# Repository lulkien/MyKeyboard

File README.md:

# My Custom Mechanical Keyboard

This is the design for my custom TLK, where I'm gonna make my own keyboard from scratch with hotswap controller.

(I have no idea why I'm doing this but it's kinda cool)

## Todo:

- [x] PCB Design (Kicad 8)
- [x] Case Design (OpenSCAD)
- [x] Firmware (use Rust)

## References:

- [Joe Scotto's guide for the PCB design](https://www.youtube.com/watch?v=7LyziNdFlew&list=PLBD2IS_t_iWZDMdG_ZF57x9Ebm3kxKqxF) (recommend to watch this playlist first)

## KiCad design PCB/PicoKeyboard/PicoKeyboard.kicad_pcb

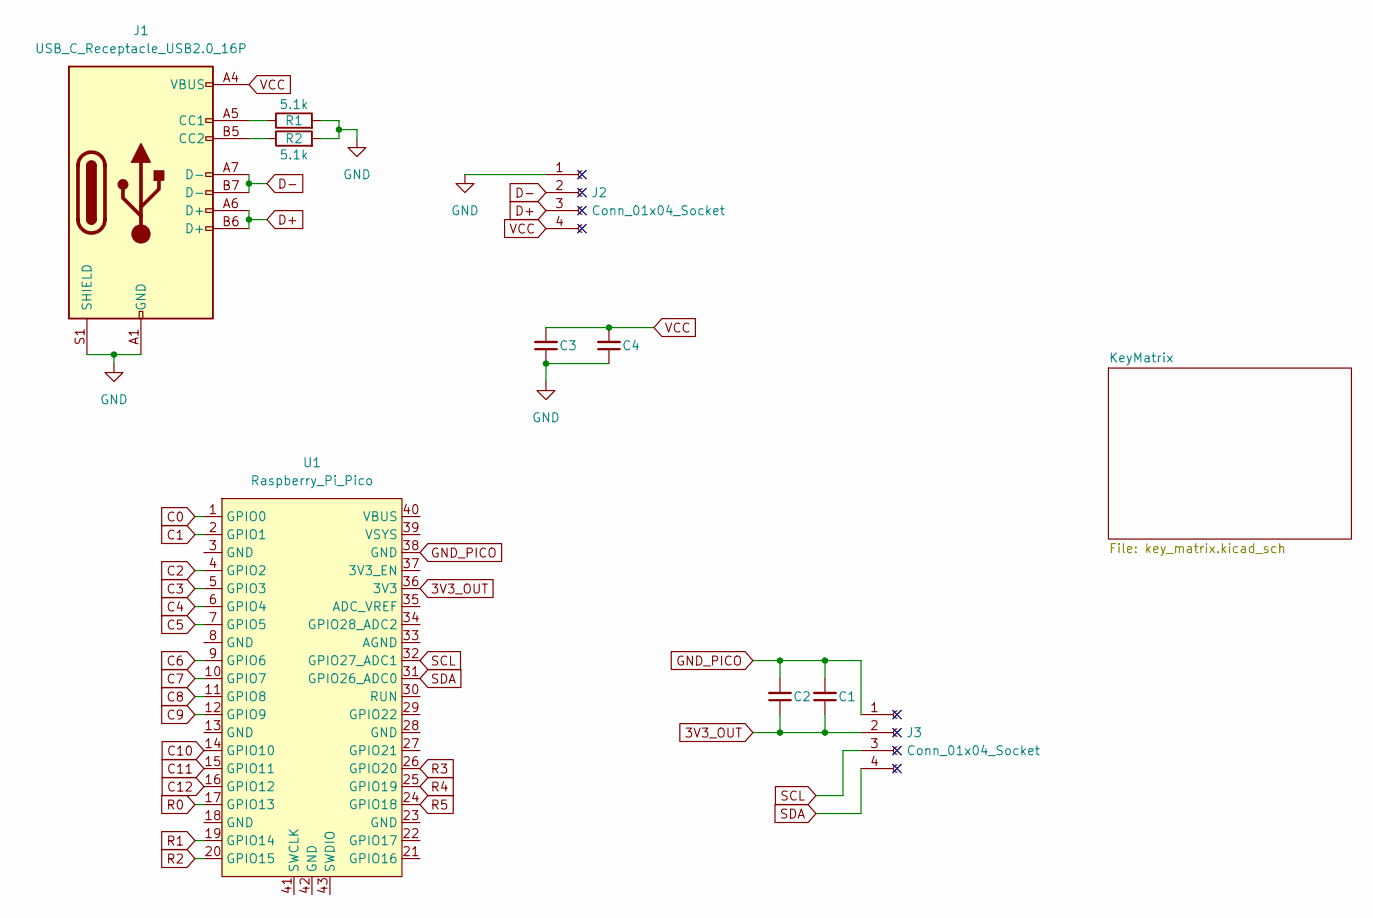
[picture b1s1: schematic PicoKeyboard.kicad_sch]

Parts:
C1, C4: 100nF; C_0603_1608Metric
C2, C3: 1uF; C_0603_1608Metric
J1: USB_C_Receptacle_USB2.0_16P; USB_C_Receptacle_HCTL_HC-TYPE-C-16P-01A
J2: Conn_01x04_Socket; PinHeader_1x04_P2.54mm_Vertical
J3: Conn_01x04_Socket; PinSocket_1x04_P2.54mm_Vertical
R1, R2: 5.1k; R_0603_1608Metric
U1: Raspberry_Pi_Pico

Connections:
3V3_OUT: C1.1, C2.1, J3.2, U1.36 (3V3)
C0: U1.1 (GPIO0); also elsewhere on the board
C1: U1.2 (GPIO1); also elsewhere on the board
C2: U1.4 (GPIO2); also elsewhere on the board
C3: U1.5 (GPIO3); also elsewhere on the board
C4: U1.6 (GPIO4); also elsewhere on the board
C5: U1.7 (GPIO5); also elsewhere on the board
C6: U1.9 (GPIO6); also elsewhere on the board
C7: U1.10 (GPIO7); also elsewhere on the board
C8: U1.11 (GPIO8); also elsewhere on the board
C9: U1.12 (GPIO9); also elsewhere on the board
C10: U1.14 (GPIO10); also elsewhere on the board
C11: U1.15 (GPIO11); also elsewhere on the board
C12: U1.16 (GPIO12); also elsewhere on the board
D+: J1.A6 (D+), J1.B6 (D+), J2.3
D-: J1.A7 (D-), J1.B7 (D-), J2.2
GND: C3.1, C4.1, J1.A1 (GND), J1.A12 (GND), J1.B1 (GND), J1.B12 (GND), J1.S1 (SHIELD), J2.1, R1.2, R2.2
GND_PICO: C1.2, C2.2, J3.1, U1.38 (GND)
unnamed: J1.A5 (CC1), R1.1
unnamed: J1.B5 (CC2), R2.1
R0: U1.17 (GPIO13); also elsewhere on the board
R1: U1.19 (GPIO14); also elsewhere on the board
R2: U1.20 (GPIO15); also elsewhere on the board
R3: U1.26 (GPIO20); also elsewhere on the board
R4: U1.25 (GPIO19); also elsewhere on the board
R5: U1.24 (GPIO18); also elsewhere on the board
SCL: J3.3, U1.32 (GPIO27_ADC1)
SDA: J3.4, U1.31 (GPIO26_ADC0)
VCC: C3.2, C4.2, J1.A4 (VBUS), J1.A9 (VBUS), J1.B4 (VBUS), J1.B9 (VBUS), J2.4

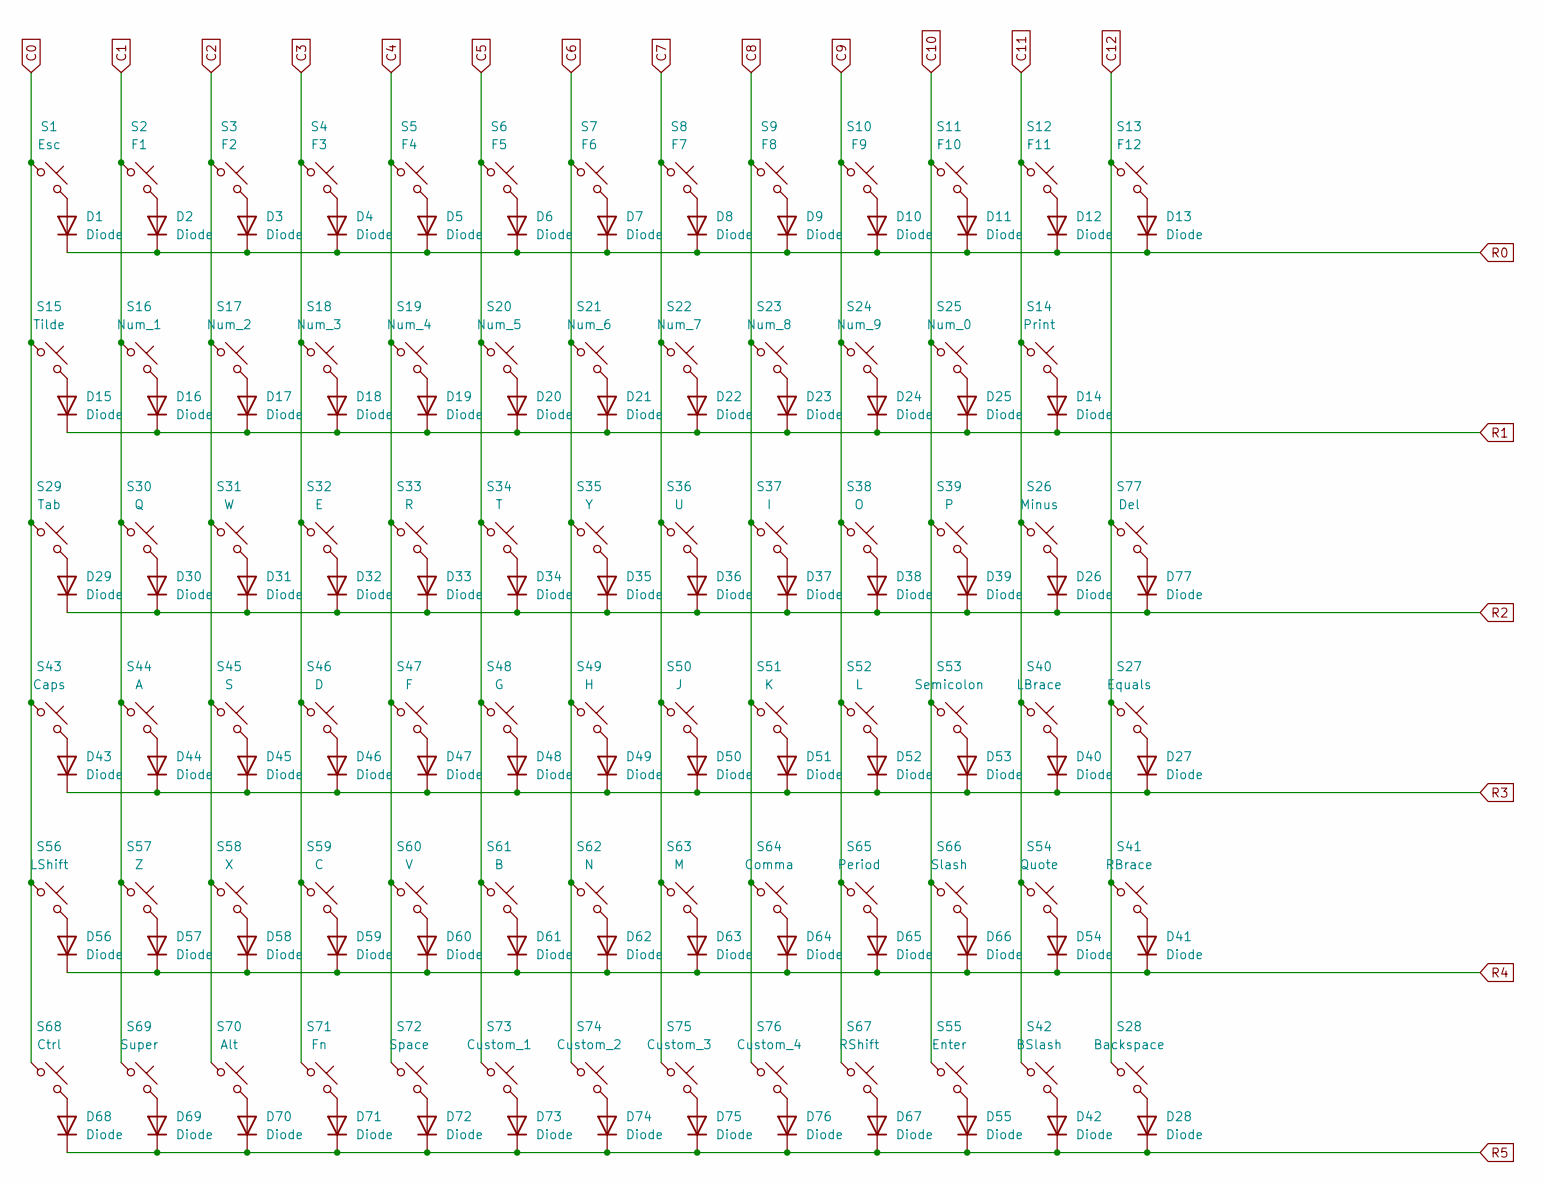
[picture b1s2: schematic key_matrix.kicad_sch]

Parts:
D1, D2, D3, D4, D5, D6, D7, D8, D9, D10, D11, D12, D13, D14, D15, D16, D17, D18, D19, D20, D21, D22, D23, D24, D25, D26, D27, D28, D29, D30, D31, D32, D33, D34, D35, D36, D37, D38, D39, D40, D41, D42, D43, D44, D45, D46, D47, D48, D49, D50, D51, D52, D53, D54, D55, D56, D57, D58, D59, D60, D61, D62, D63, D64, D65, D66, D67, D68, D69, D70, D71, D72, D73, D74, D75, D76, D77: Diode; Diode_SOD-123
S1: Esc; Hotswap_MX_1.00u
S2: F1; Hotswap_MX_1.00u
S3: F2; Hotswap_MX_1.00u
S4: F3; Hotswap_MX_1.00u
S5: F4; Hotswap_MX_1.00u
S6: F5; Hotswap_MX_1.00u
S7: F6; Hotswap_MX_1.00u
S8: F7; Hotswap_MX_1.00u
S9: F8; Hotswap_MX_1.00u
S10: F9; Hotswap_MX_1.00u
S11: F10; Hotswap_MX_1.00u
S12: F11; Hotswap_MX_1.00u
S13: F12; Hotswap_MX_1.00u
S14: Print; Hotswap_MX_1.00u
S15: Tilde; Hotswap_MX_1.00u
S16: Num_1; Hotswap_MX_1.00u
S17: Num_2; Hotswap_MX_1.00u
S18: Num_3; Hotswap_MX_1.00u
S19: Num_4; Hotswap_MX_1.00u
S20: Num_5; Hotswap_MX_1.00u
S21: Num_6; Hotswap_MX_1.00u
S22: Num_7; Hotswap_MX_1.00u
S23: Num_8; Hotswap_MX_1.00u
S24: Num_9; Hotswap_MX_1.00u
S25: Num_0; Hotswap_MX_1.00u
S26: Minus; Hotswap_MX_1.00u
S27: Equals; Hotswap_MX_1.00u
S28: Backspace; Hotswap_MX_2.00u
S29: Tab; Hotswap_MX_1.50u
S30: Q; Hotswap_MX_1.00u
S31: W; Hotswap_MX_1.00u
S32: E; Hotswap_MX_1.00u
S33: R; Hotswap_MX_1.00u
S34: T; Hotswap_MX_1.00u
S35: Y; Hotswap_MX_1.00u
S36: U; Hotswap_MX_1.00u
S37: I; Hotswap_MX_1.00u
S38: O; Hotswap_MX_1.00u
S39: P; Hotswap_MX_1.00u
S40: LBrace; Hotswap_MX_1.00u
S41: RBrace; Hotswap_MX_1.00u
S42: BSlash; Hotswap_MX_1.50u
S43: Caps; Hotswap_MX_1.75u
S44: A; Hotswap_MX_1.00u
S45: S; Hotswap_MX_1.00u
S46: D; Hotswap_MX_1.00u
S47: F; Hotswap_MX_1.00u
S48: G; Hotswap_MX_1.00u
S49: H; Hotswap_MX_1.00u
S50: J; Hotswap_MX_1.00u
S51: K; Hotswap_MX_1.00u
S52: L; Hotswap_MX_1.00u
S53: Semicolon; Hotswap_MX_1.00u
S54: Quote; Hotswap_MX_1.00u
S55: Enter; Hotswap_MX_2.25u
S56: LShift; Hotswap_MX_2.25u
S57: Z; Hotswap_MX_1.00u
S58: X; Hotswap_MX_1.00u
S59: C; Hotswap_MX_1.00u
S60: V; Hotswap_MX_1.00u
S61: B; Hotswap_MX_1.00u
S62: N; Hotswap_MX_1.00u
S63: M; Hotswap_MX_1.00u
S64: Comma; Hotswap_MX_1.00u
S65: Period; Hotswap_MX_1.00u
S66: Slash; Hotswap_MX_1.00u
S67: RShift; Hotswap_MX_2.75u
S68: Ctrl; Hotswap_MX_1.25u
S69: Super; Hotswap_MX_1.25u
S70: Alt; Hotswap_MX_1.25u
S71: Fn; Hotswap_MX_1.00u
S72: Space; Hotswap_MX_6.25u
S73: Custom_1; Hotswap_MX_1.00u
S74: Custom_2; Hotswap_MX_1.00u
S75: Custom_3; Hotswap_MX_1.00u
S76: Custom_4; Hotswap_MX_1.00u
S77: Del; Hotswap_MX_1.00u

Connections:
C0: S1.1, S15.1, S29.1, S43.1, S56.1, S68.1; also elsewhere on the board
C1: S2.1, S16.1, S30.1, S44.1, S57.1, S69.1; also elsewhere on the board
C2: S3.1, S17.1, S31.1, S45.1, S58.1, S70.1; also elsewhere on the board
C3: S4.1, S18.1, S32.1, S46.1, S59.1, S71.1; also elsewhere on the board
C4: S5.1, S19.1, S33.1, S47.1, S60.1, S72.1; also elsewhere on the board
C5: S6.1, S20.1, S34.1, S48.1, S61.1, S73.1; also elsewhere on the board
C6: S7.1, S21.1, S35.1, S49.1, S62.1, S74.1; also elsewhere on the board
C7: S8.1, S22.1, S36.1, S50.1, S63.1, S75.1; also elsewhere on the board
C8: S9.1, S23.1, S37.1, S51.1, S64.1, S76.1; also elsewhere on the board
C9: S10.1, S24.1, S38.1, S52.1, S65.1, S67.1; also elsewhere on the board
C10: S11.1, S25.1, S39.1, S53.1, S55.1, S66.1; also elsewhere on the board
C11: S12.1, S14.1, S26.1, S40.1, S42.1, S54.1; also elsewhere on the board
C12: S13.1, S27.1, S28.1, S41.1, S77.1; also elsewhere on the board
unnamed: D1.2 (A), S1.2
unnamed: D2.2 (A), S2.2
unnamed: D3.2 (A), S3.2
unnamed: D4.2 (A), S4.2
unnamed: D5.2 (A), S5.2
unnamed: D6.2 (A), S6.2
unnamed: D7.2 (A), S7.2
unnamed: D8.2 (A), S8.2
unnamed: D9.2 (A), S9.2
unnamed: D10.2 (A), S10.2
unnamed: D11.2 (A), S11.2
unnamed: D12.2 (A), S12.2
unnamed: D13.2 (A), S13.2
unnamed: D14.2 (A), S14.2
unnamed: D15.2 (A), S15.2
unnamed: D16.2 (A), S16.2
unnamed: D17.2 (A), S17.2
unnamed: D18.2 (A), S18.2
unnamed: D19.2 (A), S19.2
unnamed: D20.2 (A), S20.2
unnamed: D21.2 (A), S21.2
unnamed: D22.2 (A), S22.2
unnamed: D23.2 (A), S23.2
unnamed: D24.2 (A), S24.2
unnamed: D25.2 (A), S25.2
unnamed: D26.2 (A), S26.2
unnamed: D27.2 (A), S27.2
unnamed: D28.2 (A), S28.2
unnamed: D29.2 (A), S29.2
unnamed: D30.2 (A), S30.2
unnamed: D31.2 (A), S31.2
unnamed: D32.2 (A), S32.2
unnamed: D33.2 (A), S33.2
unnamed: D34.2 (A), S34.2
unnamed: D35.2 (A), S35.2
unnamed: D36.2 (A), S36.2
unnamed: D37.2 (A), S37.2
unnamed: D38.2 (A), S38.2
unnamed: D39.2 (A), S39.2
unnamed: D40.2 (A), S40.2
unnamed: D41.2 (A), S41.2
unnamed: D42.2 (A), S42.2
unnamed: D43.2 (A), S43.2
unnamed: D44.2 (A), S44.2
unnamed: D45.2 (A), S45.2
unnamed: D46.2 (A), S46.2
unnamed: D47.2 (A), S47.2
unnamed: D48.2 (A), S48.2
unnamed: D49.2 (A), S49.2
unnamed: D50.2 (A), S50.2
unnamed: D51.2 (A), S51.2
unnamed: D52.2 (A), S52.2
unnamed: D53.2 (A), S53.2
unnamed: D54.2 (A), S54.2
unnamed: D55.2 (A), S55.2
unnamed: D56.2 (A), S56.2
unnamed: D57.2 (A), S57.2
unnamed: D58.2 (A), S58.2
unnamed: D59.2 (A), S59.2
unnamed: D60.2 (A), S60.2
unnamed: D61.2 (A), S61.2
unnamed: D62.2 (A), S62.2
unnamed: D63.2 (A), S63.2
unnamed: D64.2 (A), S64.2
unnamed: D65.2 (A), S65.2
unnamed: D66.2 (A), S66.2
unnamed: D67.2 (A), S67.2
unnamed: D68.2 (A), S68.2
unnamed: D69.2 (A), S69.2
unnamed: D70.2 (A), S70.2
unnamed: D71.2 (A), S71.2
unnamed: D72.2 (A), S72.2
unnamed: D73.2 (A), S73.2
unnamed: D74.2 (A), S74.2
unnamed: D75.2 (A), S75.2
unnamed: D76.2 (A), S76.2
unnamed: D77.2 (A), S77.2
R0: D1.1 (K), D2.1 (K), D3.1 (K), D4.1 (K), D5.1 (K), D6.1 (K), D7.1 (K), D8.1 (K), D9.1 (K), D10.1 (K), D11.1 (K), D12.1 (K), D13.1 (K); also elsewhere on the board
R1: D14.1 (K), D15.1 (K), D16.1 (K), D17.1 (K), D18.1 (K), D19.1 (K), D20.1 (K), D21.1 (K), D22.1 (K), D23.1 (K), D24.1 (K), D25.1 (K); also elsewhere on the board
R2: D26.1 (K), D29.1 (K), D30.1 (K), D31.1 (K), D32.1 (K), D33.1 (K), D34.1 (K), D35.1 (K), D36.1 (K), D37.1 (K), D38.1 (K), D39.1 (K), D77.1 (K); also elsewhere on the board
R3: D27.1 (K), D40.1 (K), D43.1 (K), D44.1 (K), D45.1 (K), D46.1 (K), D47.1 (K), D48.1 (K), D49.1 (K), D50.1 (K), D51.1 (K), D52.1 (K), D53.1 (K); also elsewhere on the board
R4: D41.1 (K), D54.1 (K), D56.1 (K), D57.1 (K), D58.1 (K), D59.1 (K), D60.1 (K), D61.1 (K), D62.1 (K), D63.1 (K), D64.1 (K), D65.1 (K), D66.1 (K); also elsewhere on the board
R5: D28.1 (K), D42.1 (K), D55.1 (K), D67.1 (K), D68.1 (K), D69.1 (K), D70.1 (K), D71.1 (K), D72.1 (K), D73.1 (K), D74.1 (K), D75.1 (K), D76.1 (K); also elsewhere on the board

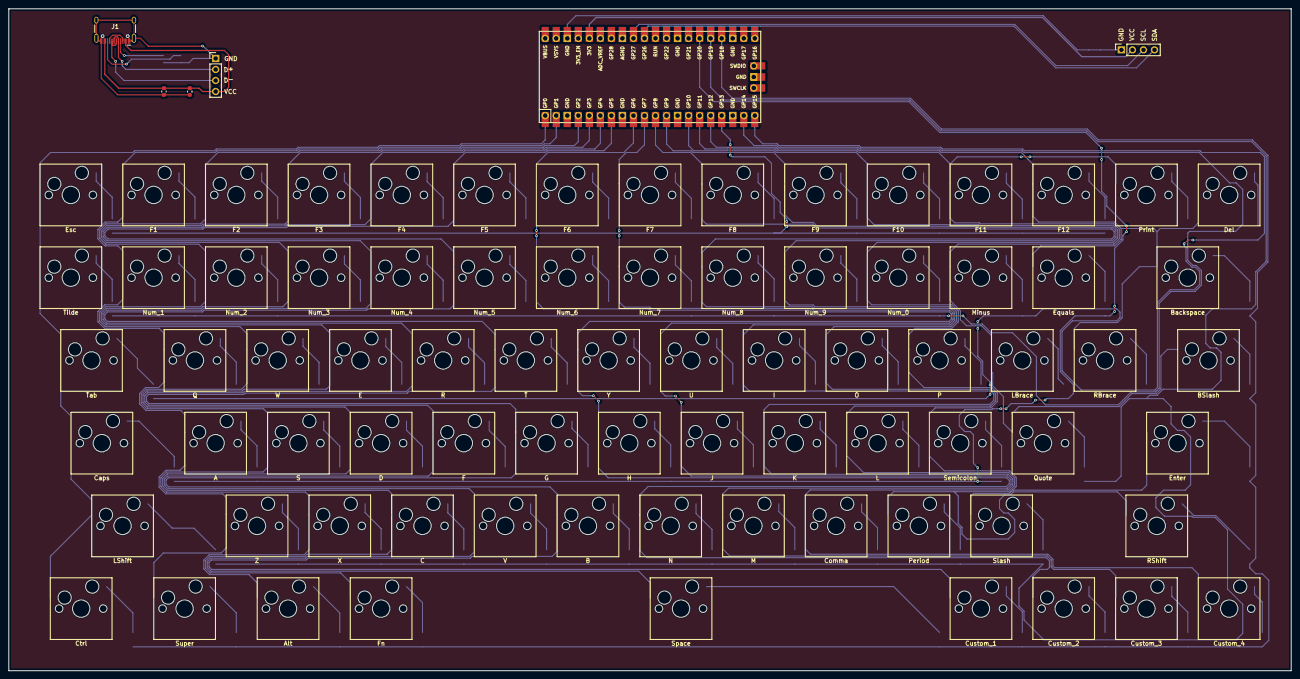
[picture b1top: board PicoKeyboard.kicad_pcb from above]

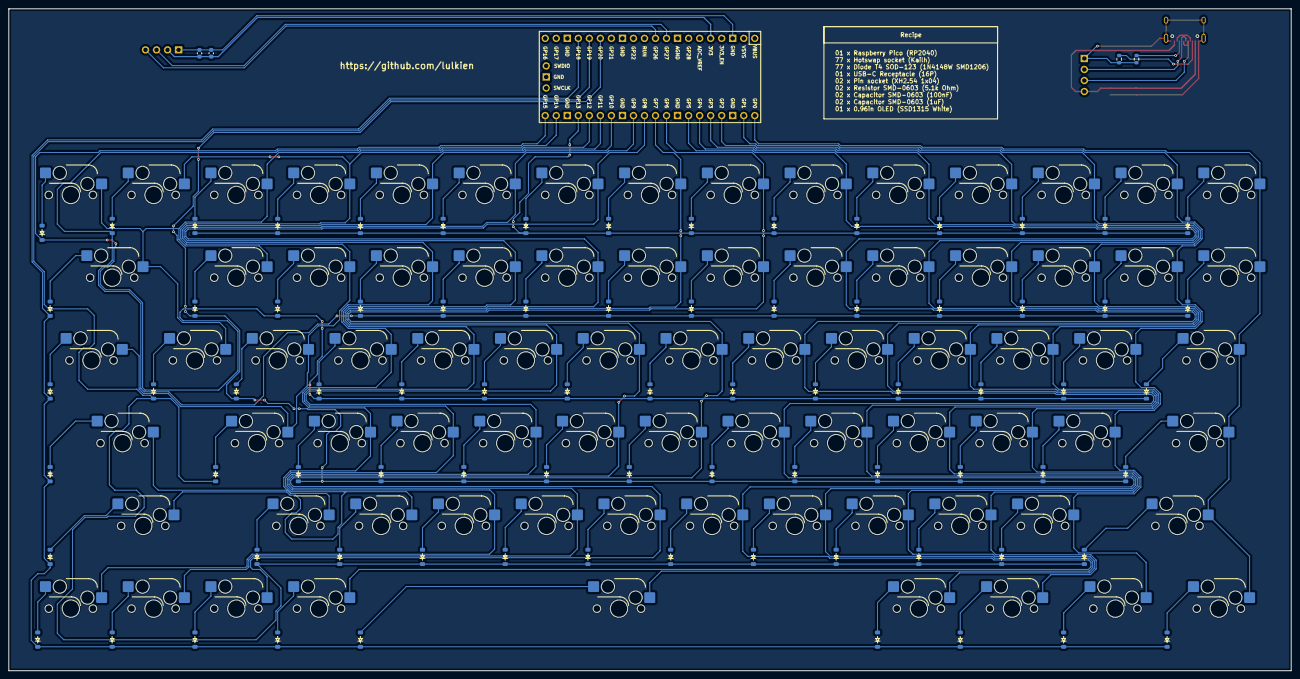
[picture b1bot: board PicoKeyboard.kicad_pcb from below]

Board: 2 copper layers, 295.3 x 152.4 mm, 164 parts (81 on the bottom side), 106 nets.

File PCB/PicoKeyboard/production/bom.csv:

Designator,Footprint,Quantity,Value,LCSC Part #
"C1, C4",0603,2,100nF,C1591
"C2, C3",0603,2,1uF,C15849
"D1, D10, D11, D12, D13, D14, D15, D16, D17, D18, D19, D2, D20, D21, D22, D23, D24, D25, D26, D27, D28, D29, D3, D30, D31, D32, D33, D34, D35, D36, D37, D38, D39, D4, D40, D41, D42, D43, D44, D45, D46, D47, D48, D49, D5, D50, D51, D52, D53, D54, D55, D56, D57, D58, D59, D6, D60, D61, D62, D63, D64, D65, D66, D67, D68, D69, D7, D70, D71, D72, D73, D74, D75, D76, D77, D8, D9",Diode_SOD-123,77,Diode,C5119556
"R1, R2",0603,2,5.1k,C23186

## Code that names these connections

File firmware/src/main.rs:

// Simple keyboard firmware. Inspired by the RustyKeys project:
// https://github.com/KOBA789/rusty-keys/blob/main/firmware/keyboard/src/bin/simple.rs

#![no_main]
#![no_std]

mod debounce;
mod hardware_config;
mod hid_class;
mod hid_descriptor;
mod key_codes;
mod key_mapping;
mod key_position;
mod key_scan;

use crate::{
    hardware_config::*,
    hid_class::HidClass,
    key_position::*,
    key_scan::{KeyboardReport, TRANSPOSED_NORMAL_LAYER_MAPPING},
};
use core::{cell::RefCell, convert::Infallible};
use cortex_m::prelude::_embedded_hal_timer_CountDown;
use critical_section::Mutex;
use debounce::Debounce;
use defmt::{error, info, warn};
use defmt_rtt as _;
use embedded_hal::digital::{InputPin, OutputPin};
use fugit::ExtU32;
use key_scan::KeyScan;
use panic_probe as _;
use rp2040_hal::{
    pac::{self, interrupt},
    usb::{self, UsbBus},
    Clock, Watchdog,
};
use usb_device::{bus::UsbBusAllocator, device::UsbDeviceBuilder, prelude::*};

/// The linker will place this boot block at the start of our program image. We
/// need this to help the ROM bootloader get our code up and running.
#[link_section = ".boot2"]
#[used]
pub static BOOT2: [u8; 256] = rp2040_boot2::BOOT_LOADER_W25Q080;

/// The USB Device Driver (shared with the interrupt).
static mut USB_DEVICE: Option<UsbDevice<usb::UsbBus>> = None;

/// The USB Bus Driver (shared with the interrupt).
static mut USB_BUS: Option<UsbBusAllocator<usb::UsbBus>> = None;

/// The USB Human Interface Device Driver (shared with the interrupt).
static USB_HID_CLASS: Mutex<RefCell<Option<HidClass<usb::UsbBus>>>> =
    Mutex::new(RefCell::new(None));

#[cortex_m_rt::entry]
fn main() -> ! {
    info!("Start of main()");
    let mut pac = pac::Peripherals::take().unwrap();
    let core = pac::CorePeripherals::take().unwrap();

    let mut watchdog = Watchdog::new(pac.WATCHDOG);

    let clocks = rp2040_hal::clocks::init_clocks_and_plls(
        EXTERNAL_CRYSTAL_FREQUENCY_HZ,
        pac.XOSC,
        pac.CLOCKS,
        pac.PLL_SYS,
        pac.PLL_USB,
        &mut pac.RESETS,
        &mut watchdog,
    )
    .ok()
    .unwrap();

    // Get the GPIO peripherals.
    let sio = rp2040_hal::Sio::new(pac.SIO);

    let pins =
        rp2040_hal::gpio::Pins::new(pac.IO_BANK0, pac.PADS_BANK0, sio.gpio_bank0, &mut pac.RESETS);

    // Set up keyboard matrix pins.
    let mut rows: [&mut dyn InputPin<Error = Infallible>; NUM_ROWS] = [
        &mut pins.gpio13.into_pull_down_input(),
        &mut pins.gpio14.into_pull_down_input(),
        &mut pins.gpio15.into_pull_down_input(),
        &mut pins.gpio20.into_pull_down_input(),
        &mut pins.gpio19.into_pull_down_input(),
        &mut pins.gpio18.into_pull_down_input(),
    ];

    let mut cols: [&mut dyn OutputPin<Error = Infallible>; NUM_COLS] = [
        &mut pins.gpio0.into_push_pull_output(),
        &mut pins.gpio1.into_push_pull_output(),
        &mut pins.gpio2.into_push_pull_output(),
        &mut pins.gpio3.into_push_pull_output(),
        &mut pins.gpio4.into_push_pull_output(),
        &mut pins.gpio5.into_push_pull_output(),
        &mut pins.gpio6.into_push_pull_output(),
        &mut pins.gpio7.into_push_pull_output(),
        &mut pins.gpio8.into_push_pull_output(),
        &mut pins.gpio9.into_push_pull_output(),
        &mut pins.gpio10.into_push_pull_output(),
        &mut pins.gpio11.into_push_pull_output(),
        &mut pins.gpio12.into_push_pull_output(),
    ];

    let mut caps_led = pins.gpio25.into_push_pull_output();

    // Initialize a delay for accurate sleeping.
    let mut delay = cortex_m::delay::Delay::new(core.SYST, clocks.system_clock.freq().to_Hz());
    let timer = rp2040_hal::Timer::new(pac.TIMER, &mut pac.RESETS, &clocks);

    let mut modifier_mask = [[false; NUM_ROWS]; NUM_COLS];
    for (col, mapping_col) in modifier_mask.iter_mut().zip(TRANSPOSED_NORMAL_LAYER_MAPPING) {
        for (key, mapping_key) in col.iter_mut().zip(mapping_col) {
            *key = mapping_key.is_modifier();
        }
    }

    // Create a global debounce state to prevent unintended rapid key double-presses.
    let mut debounce: Debounce<NUM_ROWS, NUM_COLS> = Debounce::new(DEBOUNCE_TICKS, modifier_mask);

    // Do an initial scan of the keys so that we immediately have something to report to the host when asked.
    let scan = KeyScan::scan(&mut rows, &mut cols, &mut delay, &mut debounce);

    // If the Escape key is pressed during power-on, we should go into bootloader mode.
    if scan[ESC_KEY.row][ESC_KEY.col] {
        let gpio_activity_pin_mask = 0;
        let disable_interface_mask = 0;
        info!("Escape key detected on boot, going into bootloader mode.");
        rp2040_hal::rom_data::reset_to_usb_boot(gpio_activity_pin_mask, disable_interface_mask);
    }

    info!("Initializing USB");
    // Initialize USB
    let force_vbus_detect_bit = true;
    let usb_bus = UsbBus::new(
        pac.USBCTRL_REGS,
        pac.USBCTRL_DPRAM,
        clocks.usb_clock,
        force_vbus_detect_bit,
        &mut pac.RESETS,
    );
    let bus_allocator = UsbBusAllocator::new(usb_bus);
    let bus_allocator_ref = unsafe {
        // Note (safety): This is safe as interrupts haven't been started yet
        USB_BUS = Some(bus_allocator);
        // We are promising to the compiler not to take mutable access to this global
        // variable while this reference exists!
        USB_BUS.as_ref().unwrap()
    };

    let hid_class = HidClass::new(bus_allocator_ref);

    // https://github.com/obdev/v-usb/blob/7a28fdc685952412dad2b8842429127bc1cf9fa7/usbdrv/USB-IDs-for-free.txt#L128
    let keyboard_usb_device = UsbDeviceBuilder::new(bus_allocator_ref, UsbVidPid(0x16c0, 0x27db))
        .supports_remote_wakeup(true)
        .strings(&[StringDescriptors::default().manufacturer("lulkien").product("keywi")])
        .unwrap()
        .build();

    unsafe {
        // Note (safety): This is safe as interrupts haven't been started yet
        critical_section::with(|cs| {
            USB_HID_CLASS.replace(cs, Some(hid_class));
        });

        USB_DEVICE = Some(keyboard_usb_device);
    }
    info!("Enabling USB interrupt handler");
    unsafe {
        pac::NVIC::unmask(pac::Interrupt::USBCTRL_IRQ);
    }
    info!("Entering main loop");

    let mut tick_count_down = timer.count_down();
    tick_count_down.start(1.millis());

    let mut last_report: KeyboardReport = scan.into();

    loop {
        if tick_count_down.wait().is_ok() {
            let scan = KeyScan::scan(&mut rows, &mut cols, &mut delay, &mut debounce);

            let report: KeyboardReport = scan.into();

            if report != last_report {
                critical_section::with(|cs| {
                    let mut hid_class = USB_HID_CLASS.borrow_ref_mut(cs);
                    let hid_class = hid_class.as_mut().unwrap();

                    if let Err(err) = hid_class.write_raw_report(&report.as_raw_input()) {
                        match err {
                            UsbError::WouldBlock => warn!("UsbError::WouldBlock"),
                            UsbError::ParseError => error!("UsbError::ParseError"),
                            UsbError::BufferOverflow => error!("UsbError::BufferOverflow"),
                            UsbError::EndpointOverflow => error!("UsbError::EndpointOverflow"),
                            UsbError::EndpointMemoryOverflow => {
                                error!("UsbError::EndpointMemoryOverflow")
                            },
                            UsbError::InvalidEndpoint => error!("UsbError::InvalidEndpoint"),
                            UsbError::Unsupported => error!("UsbError::Unsupported"),
                            UsbError::InvalidState => error!("UsbError::InvalidState"),
                        }
                    } else {
                        // Only assign to last_report if it was successfully reported.
                        last_report = report;
                        if last_report.is_capslock_enabled() {
                            let _ = caps_led.set_high();
                        } else {
                            let _ = caps_led.set_low();
                        }
                    }
                });
            }
        }
    }
}

/// Handle USB interrupts
#[allow(non_snake_case)]
#[interrupt]
unsafe fn USBCTRL_IRQ() {
    let usb_dev = USB_DEVICE.as_mut().unwrap();

    critical_section::with(|cs| {
        let mut hid_class = USB_HID_CLASS.borrow_ref_mut(cs);
        let hid_class = hid_class.as_mut().unwrap();

        usb_dev.poll(&mut [hid_class]);
    });
}

#[defmt::panic_handler]
fn panic() -> ! {
    cortex_m::asm::udf()
}

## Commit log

2024-05-16 Update gitignore for kicad and init commit kicad
    TODO: Add footprint for diode and wire the PCB
2024-05-18 Changed
2024-05-18 Completed prototype design for my custom keyboard
2024-05-18 Add production files for jlcpcb
2024-05-19 Update PCB
2024-05-19 Update Fabication
2024-05-19 Remove backups
2024-05-19 Rewired
2024-08-23 New layout
2024-08-24 Complete wiring
2024-09-07 Change layout
2024-09-07 Add gitignore
2024-09-08 Add Usb C header and XH 2.54 header
2024-09-08 Add early plate design
2024-09-09 Change gpio pin
2024-09-09 Add screen header pin
2024-09-18 Hotswap
2024-09-21 Add firmware
2024-09-22 Update plate design
2024-09-24 Implement Capslock led
2024-09-26 Add production file
2024-09-26 Update keycode
2024-09-28 Plate model completed
2024-09-29 Plate model completed 2
2024-10-02 Create side bar for plate and PCB holder
2024-10-03 Update size bar
2024-10-03 Add bottom part
2024-10-06 Update design
2024-10-06 Completed bottom piece
2024-10-06 Conmpleted design
2024-10-06 Completed design
2024-10-06 Update 3d design
2024-10-07 Update PCB Production
2024-10-07 Update BOM
2024-10-23 Update some keymaps
